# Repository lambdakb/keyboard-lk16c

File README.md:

# LK16C 4x4 Daisy-Chainable Keyboard PCB

## PCB

|          PCB (Front)          |         PCB (Back)          |
| :---------------------------: | :-------------------------: |
| [![PCB Front]][PCB Front PNG] | [![PCB Back]][PCB Back PNG] |

[PCB Front]: output/pcb/img/lk16c-pcb-top.svg
[PCB Front PNG]: output/pcb/img/lk16c-pcb-top.png
[PCB Back]: output/pcb/img/lk16c-pcb-bottom.svg
[PCB Back PNG]: output/pcb/img/lk16c-pcb-bottom.png

The PCB has been designed in [KiCad EDA 9.0](https://www.kicad.org/) using the [`kicad-lkbd`](https://github.com/lambdakb/kicad-lkbd) libraries and [`kbplacer`](https://github.com/adamws/kicad-kbplacer).

You can preview the project files using [KiCanvas](https://kicanvas.org/?github=https%3A%2F%2Fgithub.com%2Flambdakb%2Fkeyboard-lk16c%2Fblob%2Fmain%2Fpcb%2Flk16c-pcb.kicad_pro) directly in your browser and download the latest fabrication files for JLCPCB from the [latest release](https://github.com/lambdakb/keyboard-lk16c/releases/latest/).

The exported schematic is also available under [`output/schematics`](output/schematics/).

### PCB Order

| Parameters                       | Value                  |
| -------------------------------- | ---------------------- |
| Base Material                    | FR4                    |
| Layers                           | 2                      |
| Dimensions                       | 76.2 mm × 76.2 mm      |
| PCB Thickness                    | 1.6 mm                 |
| PCB Color [^pcb-color]           | Black                  |
| Silkscreen                       | White                  |
| Surface Finish [^surface-finish] | Lead Free HASL or ENIG |
| Copper Weight                    | 1 oz                   |
| Via Covering                     | Tented                 |
| Min Via Hole Size                | 0.3 mm                 |
| Board Outline Tolerance          | ± 0.2 mm               |

[^pcb-color]: You can select any PCB color you want but some manufacturers such as JLCPCB may charge you more for uncommon combos (such as Blue PCB + ENIG Surface Finish).
[^surface-finish]: The "HASL (with lead)" option is extremely discouraged due to the risk of lead poisoning. We strongly recommend paying the premium for the "Lead Free HASL" option.

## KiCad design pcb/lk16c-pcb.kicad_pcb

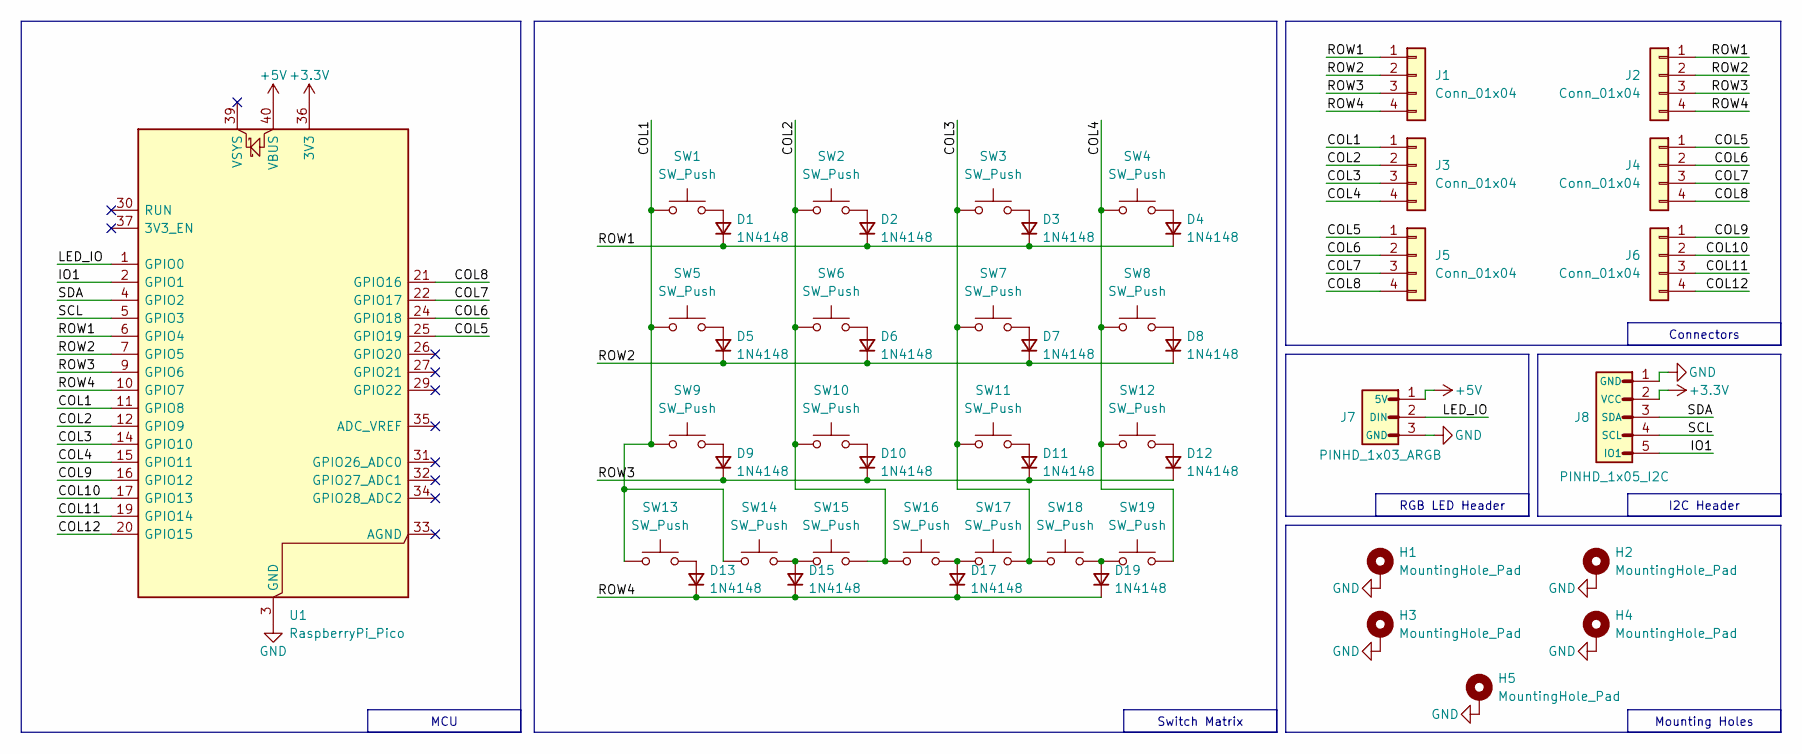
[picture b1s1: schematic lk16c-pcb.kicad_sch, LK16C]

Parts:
D1, D2, D3, D4, D5, D6, D7, D8, D9, D10, D11, D12, D13, D15, D17, D19: 1N4148; Diode_SMD_SOD-123_inSilk; LCSC C81598
H1, H2, H3, H4, H5: MountingHole_Pad; MountingHole_M2
J1, J3, J5: Conn_01x04; EdgeHeader_1x04_THT_P2.54mm_Right
J2, J4, J6: Conn_01x04; EdgeHeader_1x04_THT_P2.54mm_Left
J7: PINHD_1x03_ARGB; PinHeader_1x03_THT_P2.54mm_nSilk
J8: PINHD_1x05_I2C; PinHeader_1x05_THT_P2.54mm_nSilk
SW1, SW2, SW3, SW4, SW5, SW6, SW7, SW8, SW9, SW10, SW11, SW12, SW13, SW14, SW15, SW16, SW17, SW18, SW19: SW_Push; SW_MX_Slim_HotSwap_THT_sqSilk; JLC SMD,14.5x5.9mm
U1: RaspberryPi_Pico; MCU_RaspberryPi_Pico_THT

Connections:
+3.3V: J8.2 (VCC), U1.36 (3V3)
+5V: J7.1 (5V), U1.40 (VBUS)
/COL1: J3.1, SW1.2, SW5.2, SW9.2, SW13.2, SW14.2, U1.11 (GPIO8)
/COL2: J3.2, SW2.2, SW6.2, SW10.2, SW15.2, SW16.2, U1.12 (GPIO9)
/COL3: J3.3, SW3.2, SW7.2, SW11.2, SW17.2, SW18.2, U1.14 (GPIO10)
/COL4: J3.4, SW4.2, SW8.2, SW12.2, SW19.2, U1.15 (GPIO11)
/COL5: J4.1, J5.1, U1.25 (GPIO19)
/COL6: J4.2, J5.2, U1.24 (GPIO18)
/COL7: J4.3, J5.3, U1.22 (GPIO17)
/COL8: J4.4, J5.4, U1.21 (GPIO16)
/COL9: J6.1, U1.16 (GPIO12)
/COL10: J6.2, U1.17 (GPIO13)
/COL11: J6.3, U1.19 (GPIO14)
/COL12: J6.4, U1.20 (GPIO15)
/IO1: J8.5 (IO1), U1.2 (GPIO1)
/LED_IO: J7.2 (DIN), U1.1 (GPIO0)
/ROW1: D1.1 (K), D2.1 (K), D3.1 (K), D4.1 (K), J1.1, J2.1, U1.6 (GPIO4)
/ROW2: D5.1 (K), D6.1 (K), D7.1 (K), D8.1 (K), J1.2, J2.2, U1.7 (GPIO5)
/ROW3: D9.1 (K), D10.1 (K), D11.1 (K), D12.1 (K), J1.3, J2.3, U1.9 (GPIO6)
/ROW4: D13.1 (K), D15.1 (K), D17.1 (K), D19.1 (K), J1.4, J2.4, U1.10 (GPIO7)
/SCL: J8.4 (SCL), U1.5 (GPIO3)
/SDA: J8.3 (SDA), U1.4 (GPIO2)
GND: H1.1, H2.1, H3.1, H4.1, H5.1, J7.3 (GND), J8.1 (GND), U1.3 (GND), U1.8 (GND), U1.13 (GND), U1.18 (GND), U1.23 (GND), U1.28 (GND), U1.38 (GND)
unnamed: D1.2 (A), SW1.1
unnamed: D2.2 (A), SW2.1
unnamed: D3.2 (A), SW3.1
unnamed: D4.2 (A), SW4.1
unnamed: D5.2 (A), SW5.1
unnamed: D6.2 (A), SW6.1
unnamed: D7.2 (A), SW7.1
unnamed: D8.2 (A), SW8.1
unnamed: D9.2 (A), SW9.1
unnamed: D10.2 (A), SW10.1
unnamed: D11.2 (A), SW11.1
unnamed: D12.2 (A), SW12.1
unnamed: D13.2 (A), SW13.1
unnamed: D15.2 (A), SW14.1, SW15.1
unnamed: D17.2 (A), SW16.1, SW17.1
unnamed: D19.2 (A), SW18.1, SW19.1

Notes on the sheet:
Connectors
RGB LED Header
Mounting Holes
I2C Header
MCU
Switch Matrix

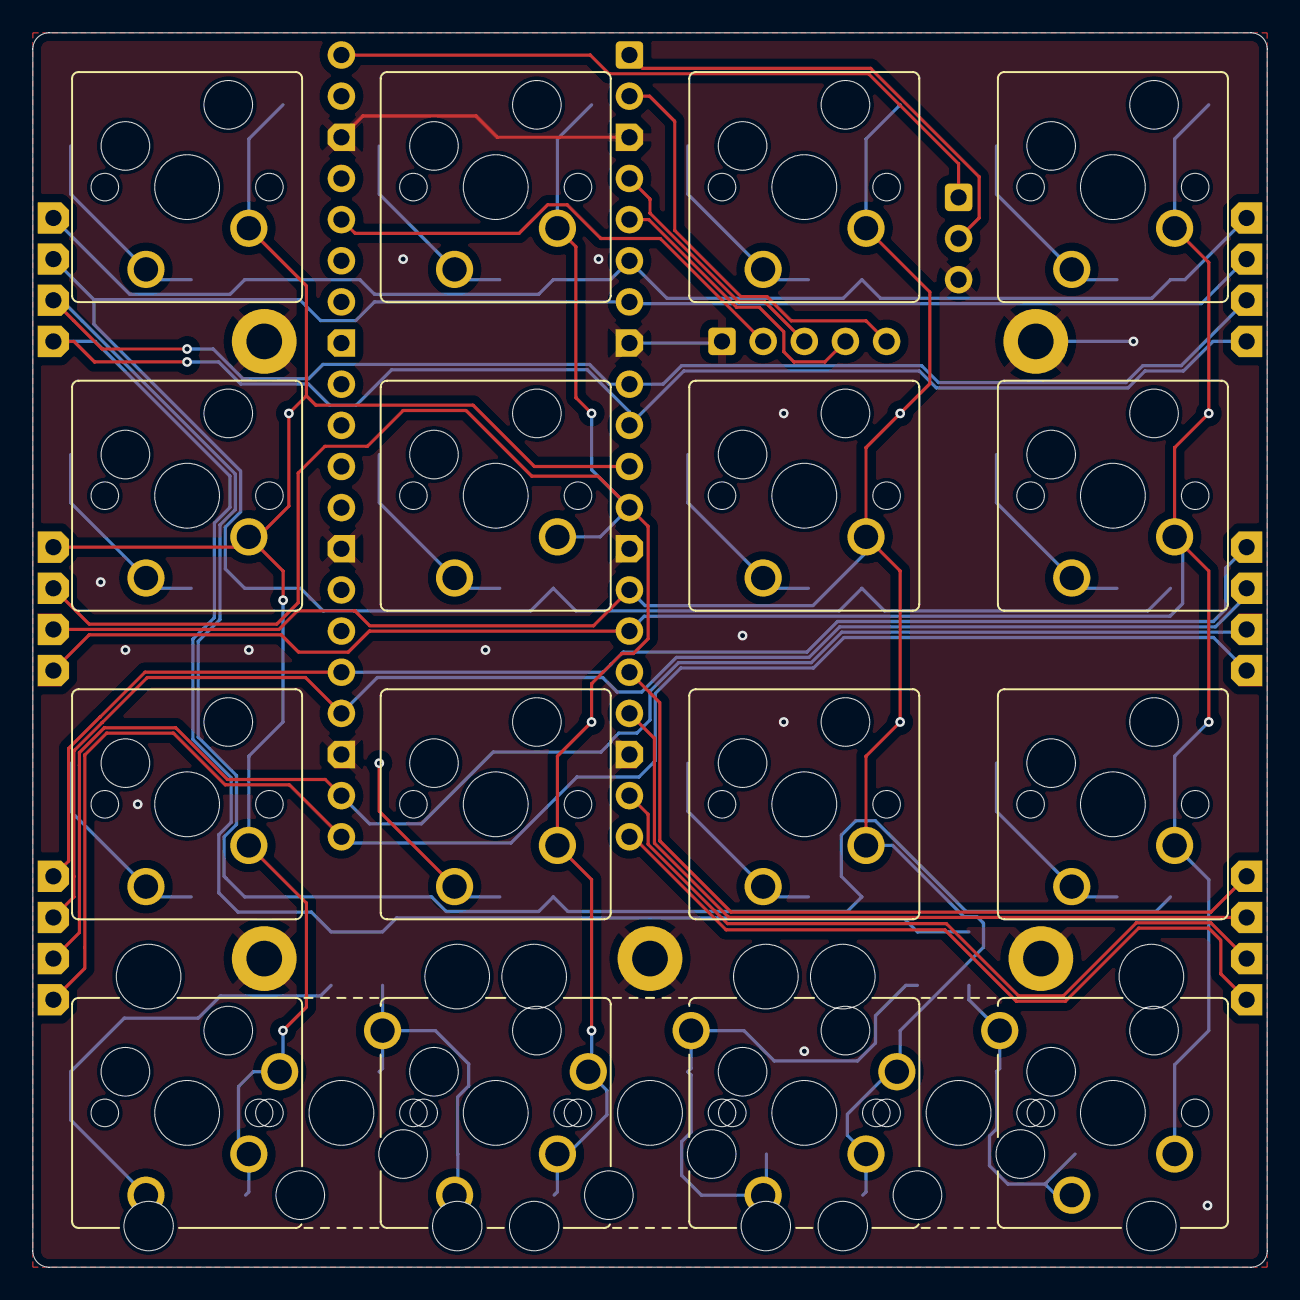
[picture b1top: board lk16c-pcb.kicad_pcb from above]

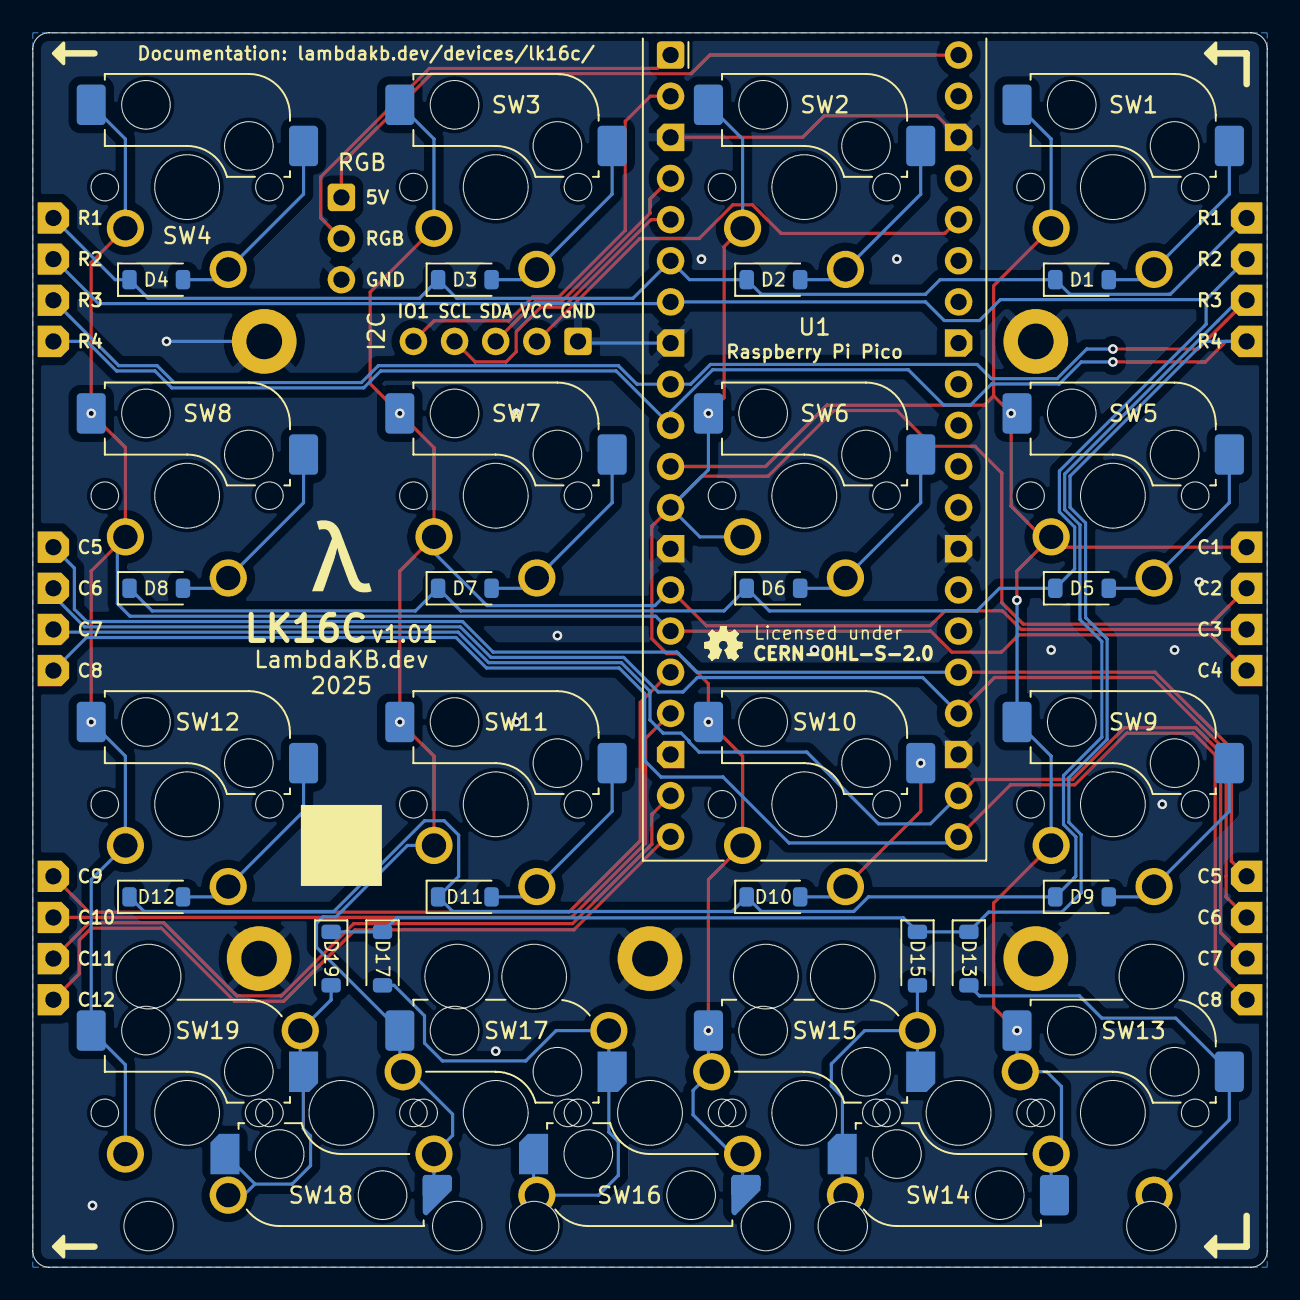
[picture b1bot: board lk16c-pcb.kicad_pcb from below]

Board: 2 copper layers, 76.2 x 76.2 mm, 53 parts (45 on the bottom side), 39 nets.

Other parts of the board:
S14, S16, S18: MX_stab; Stabilizer_MX_2U
TXT1: JLCPCB_2DBarcode_5x5mm

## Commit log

2025-05-13 Initial prototype
2025-05-14 Add plate and cleanup schematic
2025-05-14 Update board to board connector
2025-05-14 Update board to board connector (#1)
2025-05-14 Update PCB from Schematic
2025-05-23 Update LKBD and move edge connectors to leave space for an LED stirp
2025-05-23 Format README.md
2025-05-23 Update pcbdraw color
2025-05-24 Add more space between board to board connectors (#2)
    * Update LKBD and move edge connectors to leave space for an LED stirp
    * Format README.md
    * Update pcbdraw color
2025-05-24 Add ability to use 2× 2U Spacebars as the bottom row
2025-05-24 Move Fab DataMatrix footprint
2025-05-24 Add plate variant for 2space
2025-05-26 Fix mounting hole paste
2025-05-26 Add ability to use 2× 2U Spacebars as the bottom row (#3)
    * Add ability to use 2× 2U Spacebars as the bottom row
    * Move Fab DataMatrix footprint
    * Add plate variant for 2space
    * Fix mounting hole paste
2025-05-26 Bump version to v1.01

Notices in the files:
README.md:
License: CERN-OHL-S-2.0
pcb/lk16c-pcb.kicad_pcb:
CERN-OHL-S-2.0
Licensed under
